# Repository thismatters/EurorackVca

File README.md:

# Voltage Controlled Amplifier

A Voltage Controlled Amplifier amplifies an audio signal based on the voltage control signal. Can be used to shape the incoming audio to an envelope or apply tremolo (envelope not included :).

The circuit here is based on the [Yusynth VCA](https://yusynth.net/Modular/EN/VCA/index.html) with minor tweaks to make it more Eurorack friendly. The changes I've made are thus:
* Selected resistors appropriate for +/-12V rails,
* Added polarity protection so that a backward power header doesn't fry anything (twin series schotty diodes: BAT54SL),
* Selected a modern dual NPN diode package for matched transistors,
* Full surface mount design.

The Yusynth page is a treasure trove of information about this circuit that I am too amateur to claim as my own; please read that outstanding page before using this circuit. The page provides many details and other implementations of this circuit that you may find suitable.

The KiCAD project here uses the library/footprints [found in my companion repo](https://github.com/thismatters/EurorackKiCAD).

## Width

6hp on a standard 3U rack.

## Inputs

Twin control voltage inputs, the left input (marked `cv 1`) is attenuated by the `control lvl` knob.
Likewise there are two audio signal inputs, the left of these (marked `in 1`) is attenuated by the `input lvl` knob. An LED near the `input lvl` knob indicates the level of the audio input signal.
The `gain` knob overrides both CV inputs to amplify the input.

## Outputs

Twin outputs. Audio signal.

## Fiddly bits

This module can be _either_ AC or DC coupled.
For the AC coupled version build the circuit as documented.

When assembling, be sure to trim your trimmer legs pretty short lest they short on the body of the potentiometer.

### DC Coupled Version

For the DC coupled version omit the capacitors C1 and C2; short the two pins with wire (you still totally need C3 and C4 though for power regulation!).
Also use linear taper potentiometers for RV1, RV2, and RV3 (still 100kOhm) (Tayda part number `A-2963`).

## Adjustment

You'll need a dual trace oscilloscope a digital volt meter and function generator.

### Input (Cl)amping

1. Turn the `input lvl` knob to maximum (fully clockwise).
1. Turn the `gain` knob to maximum (fully clockwise).
1. Connect your function generator to the leftmost audio input (marked `in 1`) and to one of the oscilloscope channels.
1. Set up your function generator to give a 1kHz sine at 4 volts (peak to peak).
1. Connect the other oscilloscope channel to one of the outputs.
1. Adjust RV4 until the two oscilloscope traces match exactly. (If your output has flat peaks or troughs then a little tweak to RV6 will smooth those out)
1. Turn the `gain` knob to minimum (fully counterclockwise, there must also be no control voltage plugged in).
1. Adjust RV6 until there is no signal output which appears on the oscilloscope.

### DC Offset

1. Disconnect all inputs.
1. Turn all knobs to minimum (fully counterclockwise).
1. Connect your voltmeter to TP1.
1. Adjust RV5 until the voltmeter reads 0V.

## Vendors

There are part numbers in the [BOM](vca.csv) for many of the parts (not for basic passives though) at the following vendors:

* [Mouser](https://www.mouser.com): Needs no introduction. Get your ICs from here (or [digikey](https://www.digikey.com)).
* [Tayda Electronics](https://www.taydaelectronics.com/): Good supplier for passive components; audio jacks, and potentiometers. Their audio jacks are slightly smaller than the thonkiconn from thonk.
* [Love My Switches](https://lovemyswitches.com/): Has [really good knobs](https://lovemyswitches.com/anodized-aluminum-knob-the-lo-fi-1-4-smooth-shaft-12-5mm-od/) to go on those potentiometers!
* [OSHPark](https://oshpark.com/): Fast and (relatively) cheap PCB manufacturer. The [V1 circuit](https://oshpark.com/shared_projects/VmwAFYtq) works well.

## Changelog

### V2a

- [x] Updated to use correct SMD discrete transistors footprint :facepalm:

### V2

- [x] Switched to NPN for driving LED
- [x] Updated design language (redid board layout too!)
- [x] Switched to SMD discrete transistors
- [x] Corrected BOM issues

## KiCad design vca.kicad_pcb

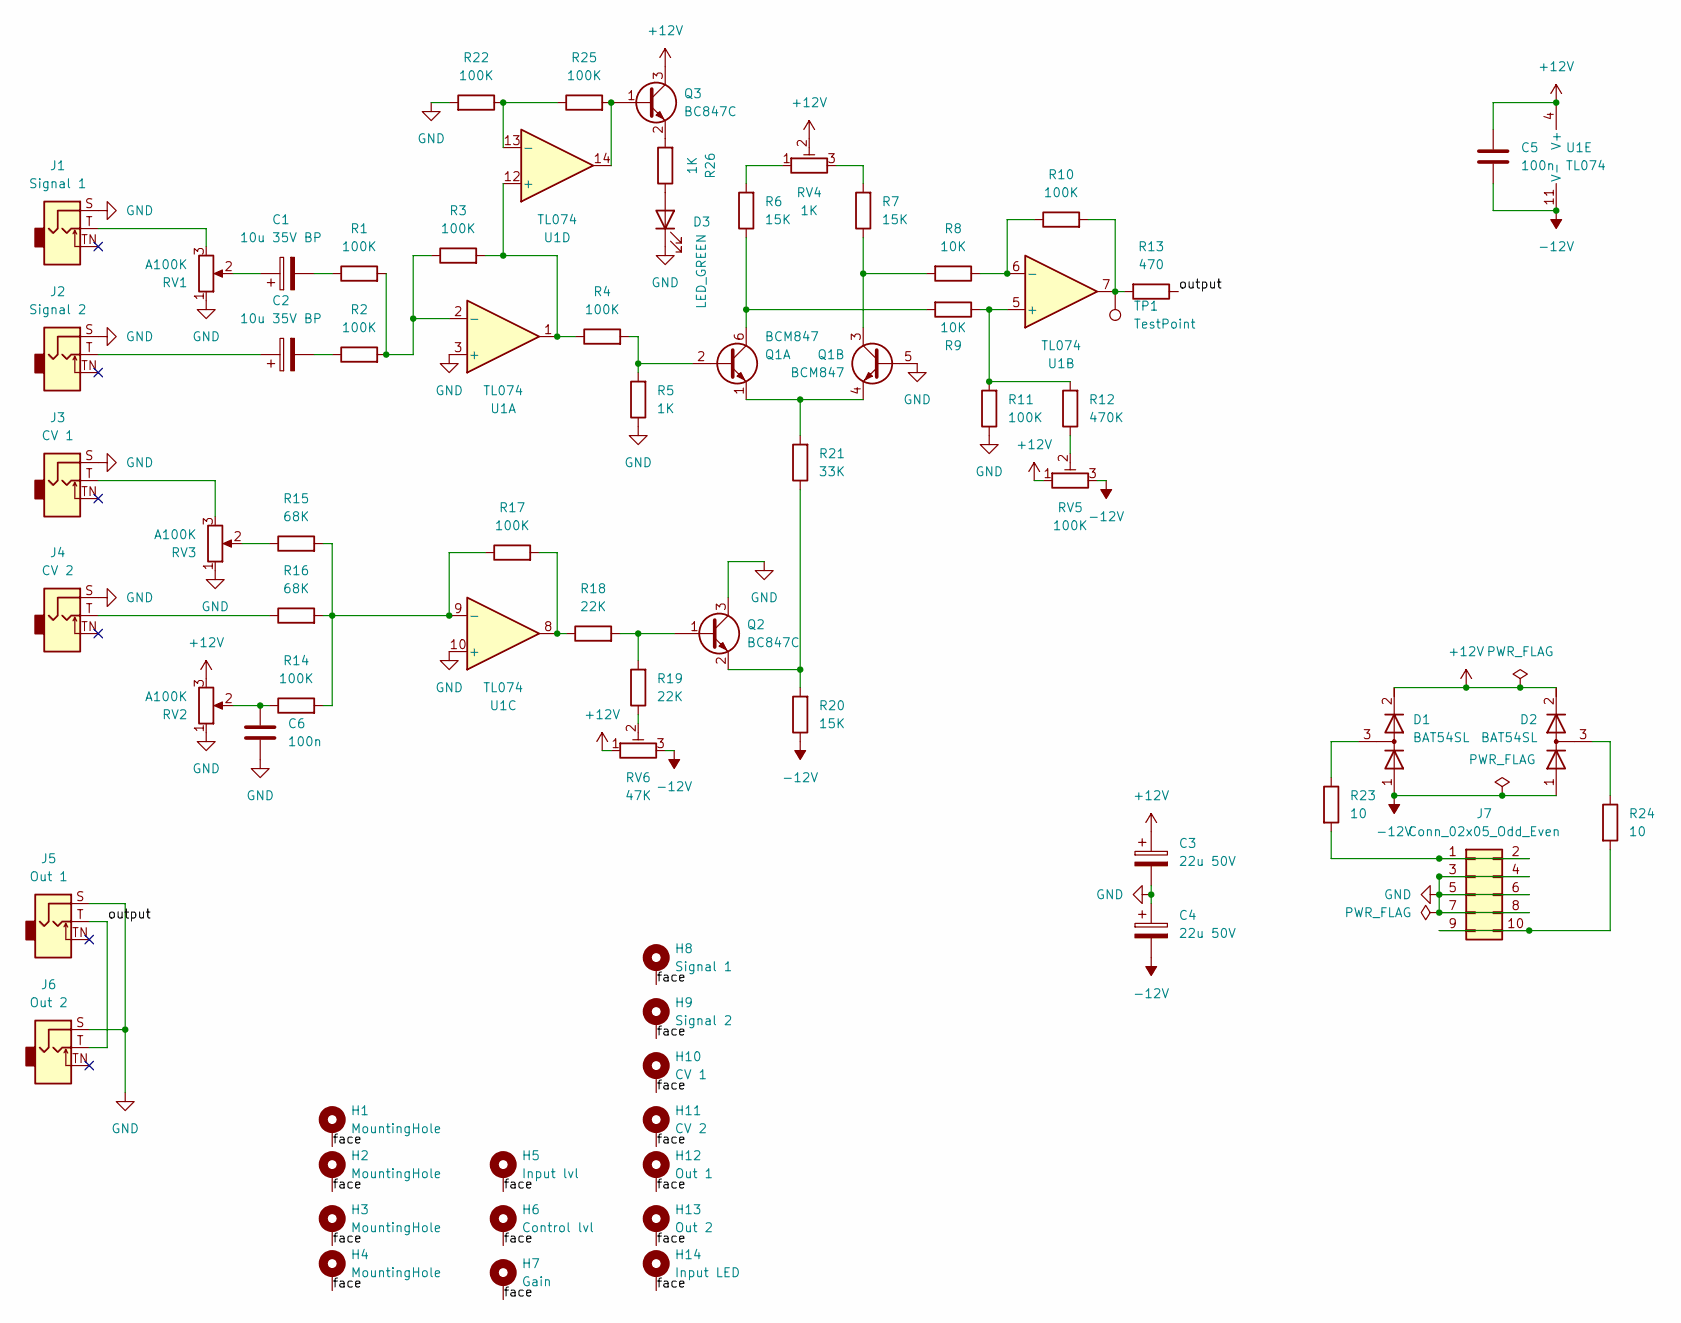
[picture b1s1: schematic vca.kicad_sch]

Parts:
C1, C2: 10u 35V BP; CP_Radial_D5.0mm_P2.50mm
C3, C4: 22u 50V; CP_Radial_D5.0mm_P2.50mm
C5, C6: 100n; C_0805_2012Metric
D1, D2: BAT54SL; SOT-23; PartNum 863-BAT54SLT1G
D3: LED_GREEN; LED_D3.0mm
H1, H2, H3, H4: MountingHole; Mech-MountingHole
H5: Input lvl; Mech-Potentiometer-Hole_level
H6: Control lvl; Mech-Potentiometer-Hole_level
H7: Gain; Mech-Potentiometer-Hole_level
H8: Signal 1; Mech-AudioJack-Hole-Input
H9: Signal 2; Mech-AudioJack-Hole-Input
H10: CV 1; Mech-AudioJack-Hole-Input-CV
H11: CV 2; Mech-AudioJack-Hole-Input-CV
H12: Out 1; Mech-AudioJack-Hole-Output
H13: Out 2; Mech-AudioJack-Hole-Output
H14: Input LED; Mech-LED-Hole-3mm-Bezel
J1: Signal 1; AudioJack2_Tayda_A-2566; PartNum A-2566
J2: Signal 2; AudioJack2_Tayda_A-2566; PartNum A-2566
J3: CV 1; AudioJack2_Tayda_A-2566; PartNum A-2566
J4: CV 2; AudioJack2_Tayda_A-2566; PartNum A-2566
J5: Out 1; AudioJack2_Tayda_A-2566; PartNum A-2566
J6: Out 2; AudioJack2_Tayda_A-2566; PartNum A-2566
J7: Conn_02x05_Odd_Even; PinHeader_2x05_P2.54mm_Vertical; PartNum A-2939
Q1: BCM847; TSOP-6_1.65x3.05mm_P0.95mm; PartNum 771-BCM847DS135
Q2, Q3: BC847C; SOT-23; PartNum 621-BC847C-13-F
R1, R2, R3, R4, R10, R11, R14, R17, R22, R25: 100K; R_0805_2012Metric
R5, R26: 1K; R_0805_2012Metric
R6, R7, R20: 15K; R_0805_2012Metric
R8, R9: 10K; R_0805_2012Metric
R12: 470K; R_0805_2012Metric
R13: 470; R_0805_2012Metric
R15, R16: 68K; R_0805_2012Metric
R18, R19: 22K; R_0805_2012Metric
R21: 33K; R_0805_2012Metric
R23, R24: 10; R_0805_2012Metric
RV1, RV2, RV3: A100K; Potentiometer_RV16AF-41-15R1; PartNum A-5407
RV4: 1K; Potentiometer_Bourns_3296W_Vertical; PartNum A-585
RV5: 100K; Potentiometer_Bourns_3296W_Vertical; PartNum A-587
RV6: 47K; Potentiometer_Bourns_3296W_Vertical; PartNum A-598
TP1: TestPoint; TestPoint_Plated_Hole_D2.0mm; PartNum 595-TL074CDR
U1: TL074; SOIC-14_3.9x8.7mm_P1.27mm; PartNum 595-TL074CDR

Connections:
+12V: C3.1, C5.1, D1.2 (K), D2.2 (K), Q3.3 (C), RV2.3, RV4.2, RV5.1, RV6.1, U1.4 (V+)
-12V: C4.2, C5.2, D1.1 (A), D2.1 (A), R20.1, RV5.3, RV6.3, U1.11 (V-)
/face: H1.1, H2.1, H3.1, H4.1, H5.1, H6.1, H7.1, H8.1, H9.1, H10.1, H11.1, H12.1, H13.1, H14.1
/output: J5.T, J6.T, R13.1
GND: C3.2, C4.1, C6.2, D3.1 (K), J1.S, J2.S, J3.S, J4.S, J5.S, J6.S, J7.3, J7.4, J7.5, J7.6, J7.7, J7.8, Q1.5 (B2), Q2.3 (C), R5.1, R11.1, R22.2, RV1.1, RV2.1, RV3.1, U1.3 (+), U1.10 (+)
unnamed: C1.1, RV1.2
unnamed: C1.2, R1.1
unnamed: C2.1, J2.T
unnamed: C2.2, R2.1
unnamed: C6.1, R14.1, RV2.2
unnamed: D1.3 (common), R23.1
unnamed: D2.3 (common), R24.1
unnamed: D3.2 (A), R26.1
unnamed: J1.T, RV1.3
unnamed: J3.T, RV3.3
unnamed: J4.T, R16.1
unnamed: J7.1, J7.2, R23.2
unnamed: J7.9, J7.10, R24.2
unnamed: Q1.2 (B1), R4.2, R5.2
unnamed: Q1.6 (C1), R6.1, R9.2
unnamed: Q1.1 (E1), Q1.4 (E2), R21.2
unnamed: Q1.3 (C2), R7.1, R8.2
unnamed: Q2.2 (E), R20.2, R21.1
unnamed: Q2.1 (B), R18.2, R19.2
unnamed: Q3.2 (E), R26.2
unnamed: Q3.1 (B), R25.2, U1.14
unnamed: R6.2, RV4.1
unnamed: R7.2, RV4.3
unnamed: R10.2, R13.2, TP1.1, U1.7
unnamed: R12.1, RV5.2
unnamed: R15.1, RV3.2
unnamed: R17.2, R18.1, U1.8
unnamed: R19.1, RV6.2
unnamed: R1.2, R2.2, R3.1, U1.2 (-)
unnamed: R9.1, R11.2, R12.2, U1.5 (+)
unnamed: R8.1, R10.1, U1.6 (-)
unnamed: R14.2, R15.2, R16.2, R17.1, U1.9 (-)
unnamed: R3.2, R4.1, U1.1, U1.12 (+)
unnamed: R22.1, R25.1, U1.13 (-)

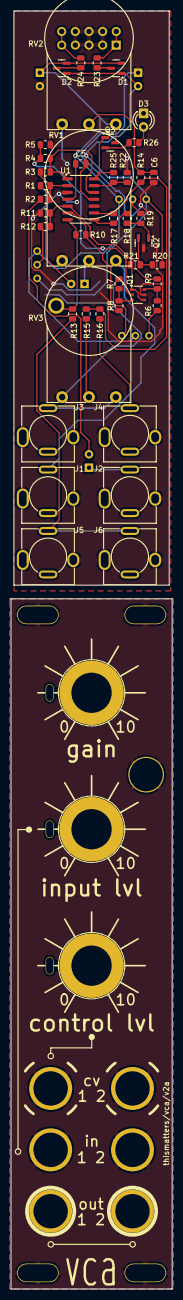
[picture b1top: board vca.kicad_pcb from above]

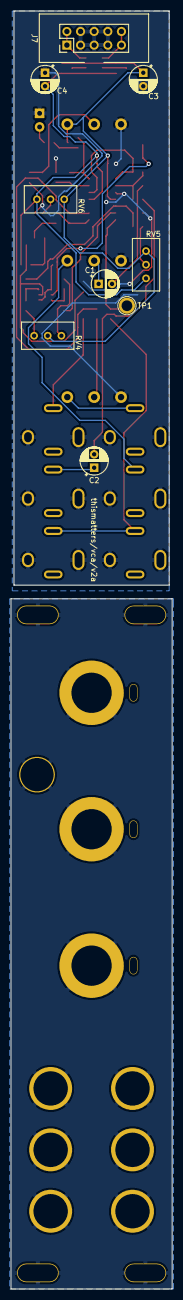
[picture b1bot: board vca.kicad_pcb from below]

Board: 2 copper layers, 30.0 x 237.9 mm, 67 parts (9 on the bottom side), 39 nets.

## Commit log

2024-01-01 initial commit -- breadboard tested circuit
2024-01-02 prepping for initial manu
2024-01-15 sent to manu
2024-11-24 adding pcb link
2025-02-02 add schematic pdf
2025-12-31 v2 ready
2026-01-01 correcting some BOM issues
2026-01-30 v2 actually ready for manu
2026-01-30 one last BOM issue
2026-02-01 use bipolar resistor at input
2026-04-28 bugfixes, update to kicad version 10
